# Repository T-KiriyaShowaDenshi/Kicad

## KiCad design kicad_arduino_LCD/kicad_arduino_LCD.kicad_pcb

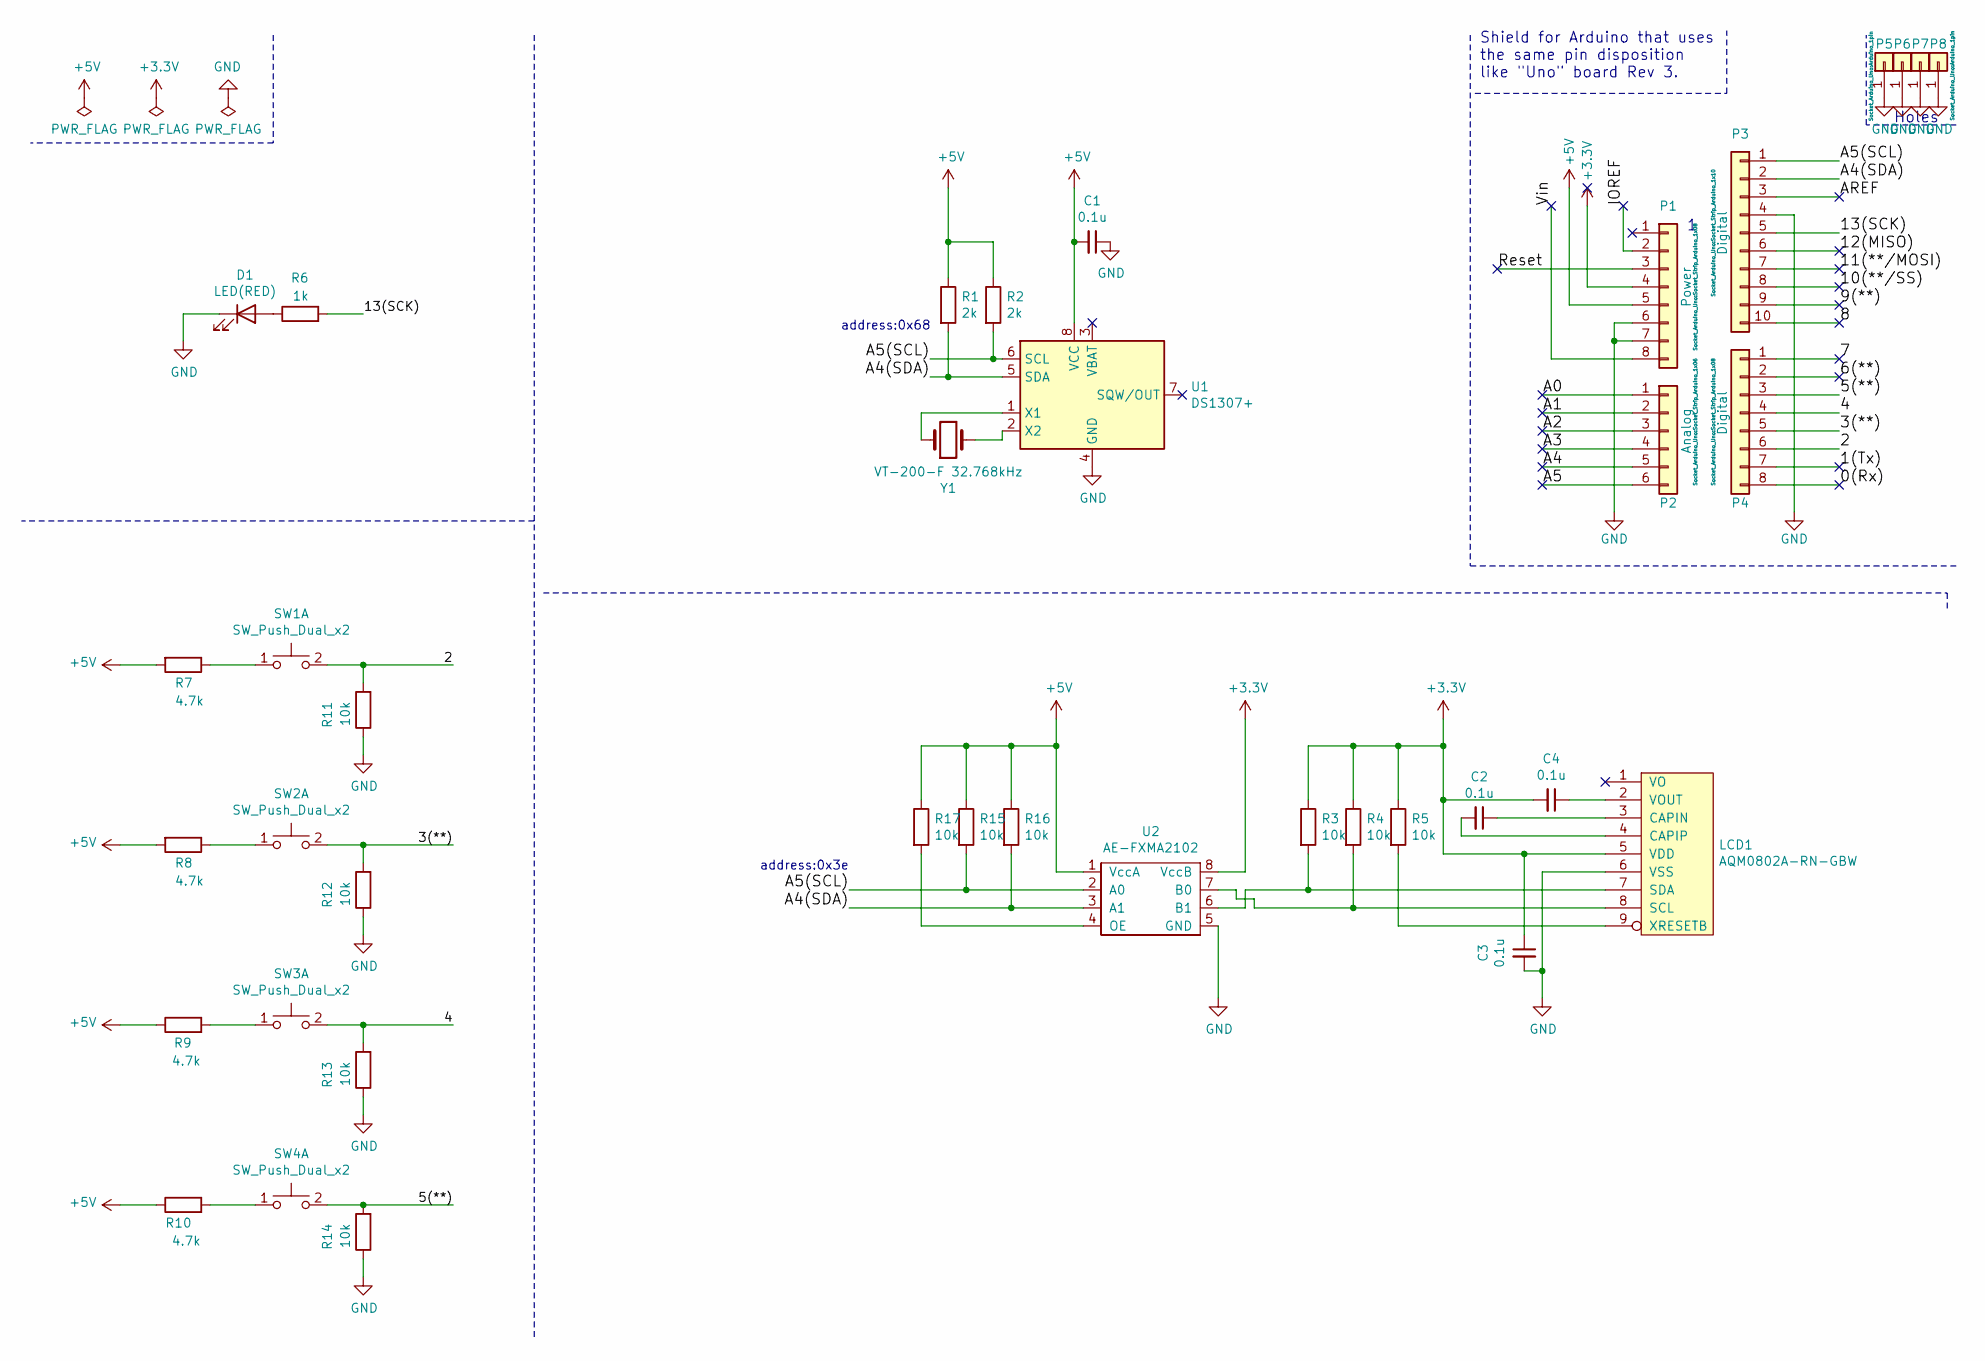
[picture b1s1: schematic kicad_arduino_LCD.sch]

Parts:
C1, C2, C3, C4: 0.1u; 1608
D1: LED(RED); LED_5mm
LCD1: AQM0802A-RN-GBW; lcd_AQM0802A-RN-GBW
P1: Power; Socket_Strip_Arduino_1x08
P2: Analog; Socket_Strip_Arduino_1x06
P3: Digital; Socket_Strip_Arduino_1x10
P4: Digital; Socket_Strip_Arduino_1x08
P5, P6, P7, P8: CONN_01X01; Arduino_1pin
R1, R2: 2k; 1608
R3, R4, R5, R11, R12, R13, R14, R15, R16, R17: 10k; 1608
R6: 1k; 1608
R7, R8, R9, R10: 4.7k; 1608
SW1, SW2, SW3, SW4: SW_Push_Dual_x2; TactSwitch
U1: DS1307+; ic_DIP-8_W7.62mm
U2: AE-FXMA2102; ic_DIP-8_W7.62mm
Y1: VT-200-F 32.768kHz; Crystal_DS26_D2.0mm_L6.0mm_Horizontal

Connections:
+3V3: C3.1, C4.2, LCD1.5 (VDD), P1.4, R3.1, R4.1, R5.1, U2.8 (VccB)
+5V: C1.2, P1.5, R1.1, R2.1, R7.2, R8.2, R9.1, R10.1, R15.1, R16.1, R17.1, U1.8 (VCC), U2.1 (VccA)
/0(Rx): P4.8
/1(Tx): P4.7
/2: P4.6, R11.2, SW1.2 (D)
/3(**): P4.5, R12.2, SW2.2 (D)
/4: P4.4, R13.2, SW3.2 (D)
/5(**): P4.3, R14.2, SW4.2 (D)
/6(**): P4.2
/7: P4.1
/8: P3.10
/9(**): P3.9
/10(**/SS): P3.8
/11(**/MOSI): P3.7
/12(MISO): P3.6
/13(SCK): P3.5, R6.2
/A0: P2.1
/A1: P2.2
/A2: P2.3
/A3: P2.4
/A4: P2.5
/A4(SDA): P3.2, R1.2, R16.2, U1.5 (SDA), U2.3 (A1)
/A5: P2.6
/A5(SCL): P3.1, R2.2, R15.2, U1.6 (SCL), U2.2 (A0)
/AREF: P3.3
/IOREF: P1.2
/Reset: P1.3
/Vin: P1.8
GND: C1.1, C3.2, D1.1 (K), LCD1.6 (VSS), P1.6, P1.7, P3.4, P5.1, P6.1, P7.1, P8.1, R11.1, R12.1, R13.1, R14.1, U1.4 (GND), U2.5 (GND)
unnamed: C2.1, LCD1.3 (CAPIN)
unnamed: C2.2, LCD1.4 (CAPIP)
unnamed: C4.1, LCD1.2 (VOUT)
unnamed: D1.2 (A), R6.1
unnamed: LCD1.7 (SDA), R3.2, U2.6 (B1)
unnamed: LCD1.8 (SCL), R4.2, U2.7 (B0)
unnamed: LCD1.9 (XRESETB), R5.2
unnamed: R7.1, SW1.1 (C)
unnamed: R8.1, SW2.1 (C)
unnamed: R9.2, SW3.1 (C)
unnamed: R10.2, SW4.1 (C)
unnamed: R17.2, U2.4 (OE)
unnamed: U1.1 (X1), Y1.1
unnamed: U1.2 (X2), Y1.2

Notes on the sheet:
Shield for Arduino that uses the same pin disposition like "Uno" board Rev 3.
Holes
address:0x68
address:0x3e

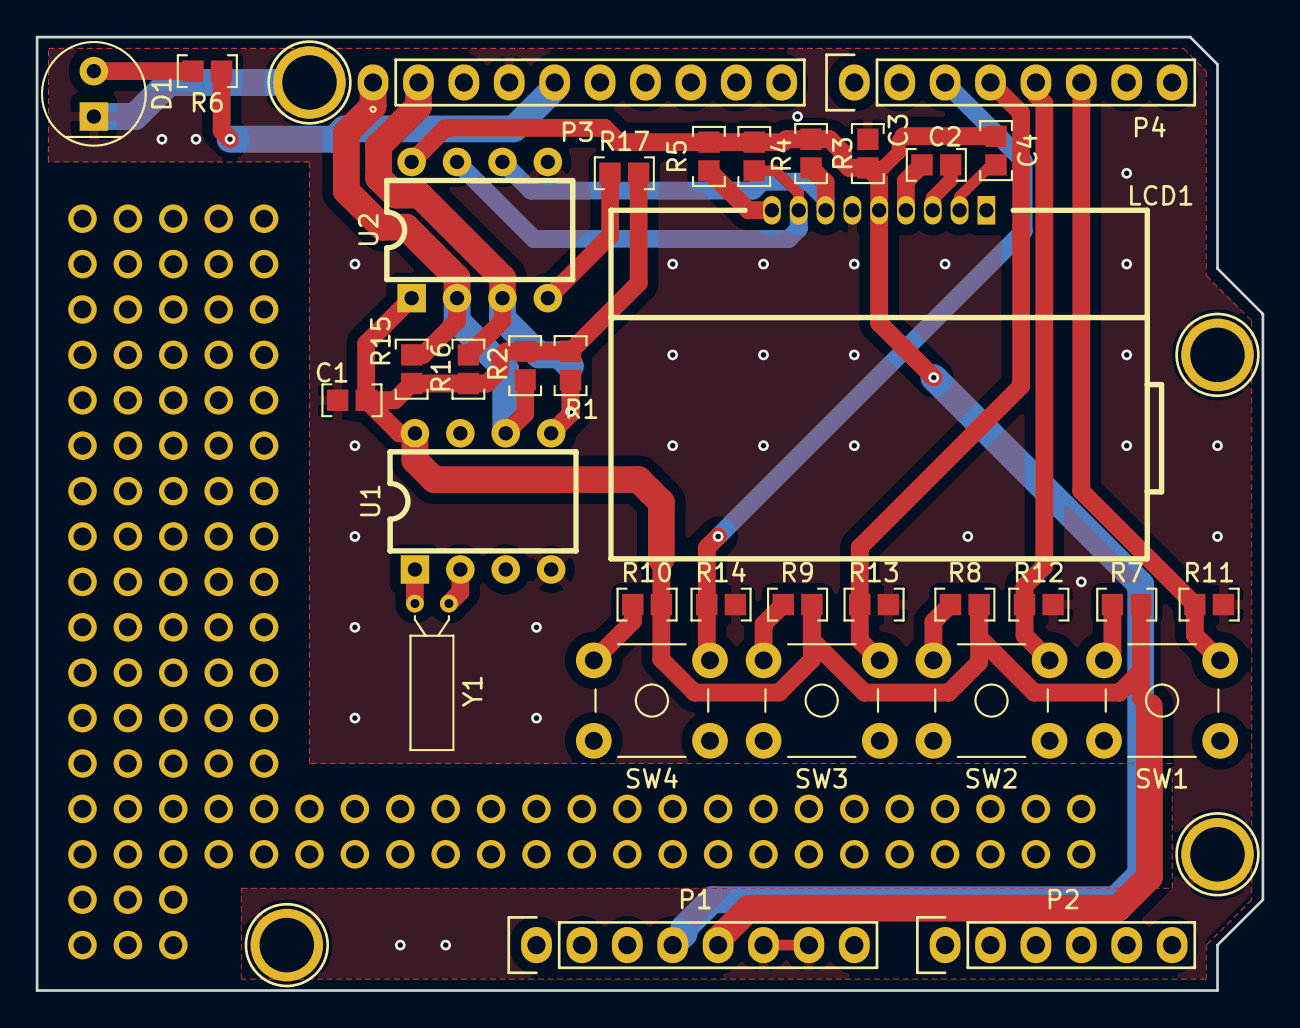
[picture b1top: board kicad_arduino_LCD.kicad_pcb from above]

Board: 2 copper layers, 68.6 x 53.3 mm, 38 parts (0 on the bottom side), 24 nets.

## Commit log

2021-12-02 Arduino用シールド基板（LCD、RTCモジュール）
2021-12-02 Arduino用シールド基板（LCD&RTCモジュール）
2021-12-10 パッドと重なったシルクを削除、Designed by T.kiriya のシルクを追加
2021-12-10 外形寸法の記入
2021-12-13 部品表を更新（Y1：VT-200→NC38）
